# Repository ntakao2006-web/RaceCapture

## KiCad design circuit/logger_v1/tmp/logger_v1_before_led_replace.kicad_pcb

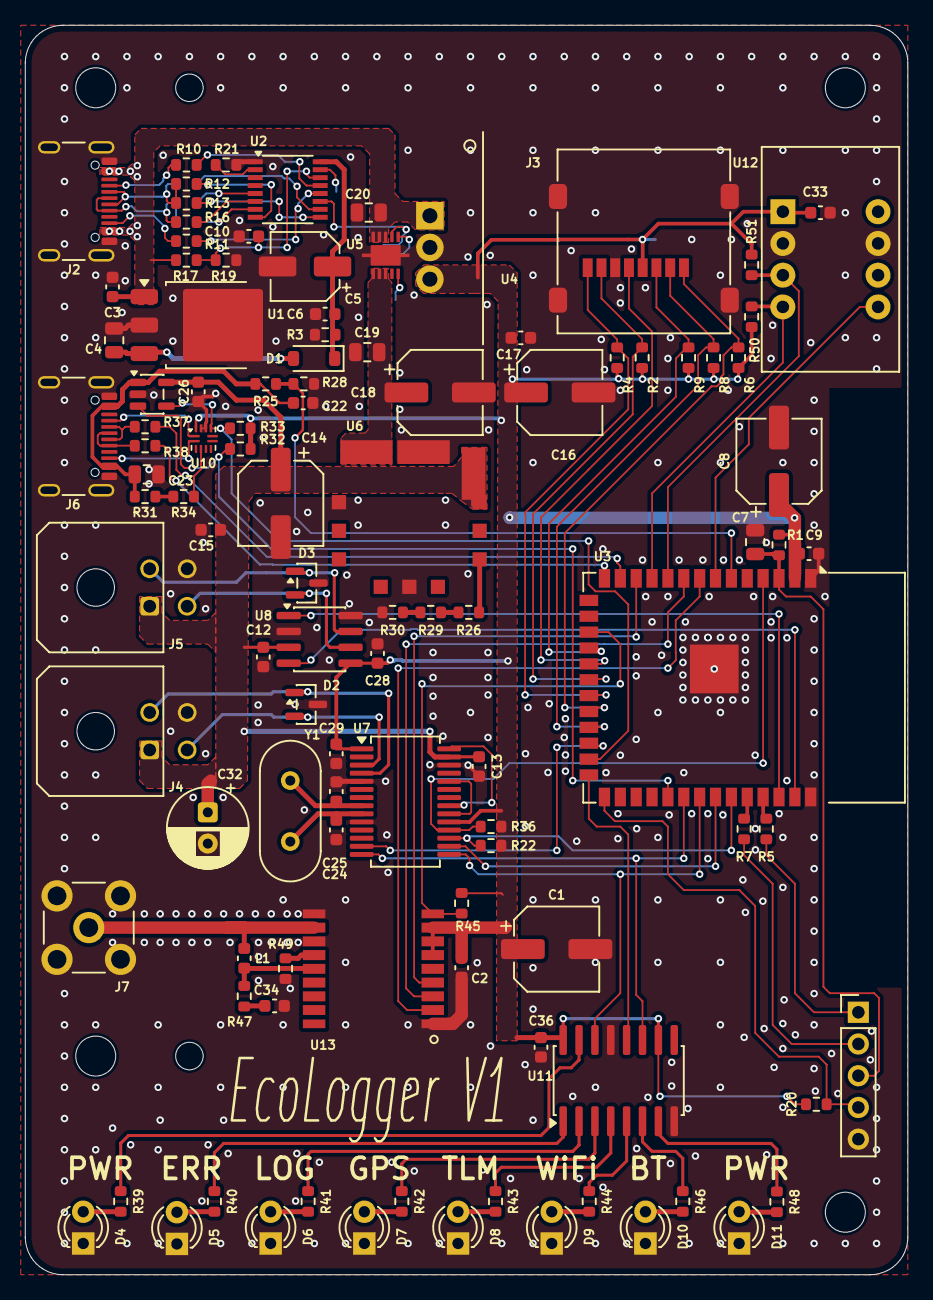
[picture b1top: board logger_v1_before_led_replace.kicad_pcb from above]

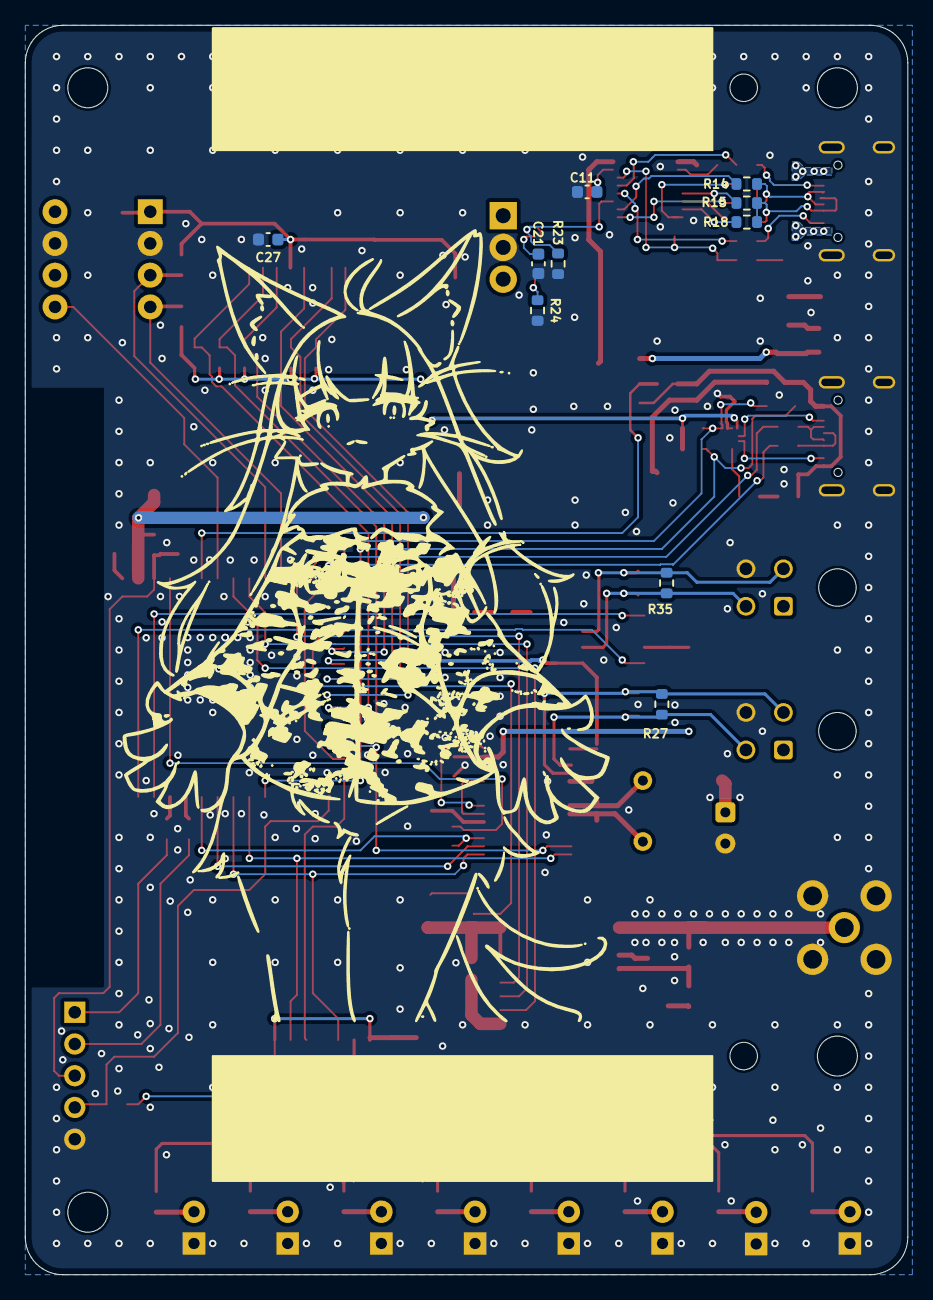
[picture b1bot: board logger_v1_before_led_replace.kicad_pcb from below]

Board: 2 copper layers, 70.6 x 100.0 mm, 123 parts (10 on the bottom side), 96 nets.

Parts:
C1, C8, C14, C16, C18: 47u; CP_Elec_6.3x5.8
C2, C3, C6, C9, C10, C12, C13, C15, C17, C22, C26, C27, C28, C29, C33, C36: 0.1u; C_0603_1608Metric
C4: 4.7u; C_0805_2012Metric
C5: 22u; CP_Elec_5x5.4
C7, C19, C20, C23: 1u; C_0805_2012Metric
C11, C21: 1n; C_0603_1608Metric
C24, C25: 33p; C_0603_1608Metric
C32: 100u; CP_Radial_D6.3mm_P2.50mm
C34: 10nF; C_0603_1608Metric
D1: PMEG4010CEGWJ; D_SOD-123
D2, D3: PEC3824C2A-AU; SOT-23
D4, D5, D6, D7, D8, D9, D10, D11: LED_Small_Filled; LED_D3.0mm
H1, H2: MountingHole; MountingHole_2.2mm_M2
H3, H4, H5, H6: MountingHole; MountingHole_3.2mm_M3
J1: Conn_01x05_Pin; PinHeader_1x05_P2.54mm_Vertical
J2, J6: 5077CR-16-SMC2-BK-TR; USB_C_5077CR-16-SMC2-BK-TR
J3: 47219-2001; Molex_47219-2001
J4, J5: 43045-0400; Molex_Micro-Fit_3.0_43045-0400_2x02_P3.00mm_Horizontal
J7: S-037-TGG; SMA_S-037-TGG_Horizontal
L1: LQW18AN27NJ00D; L_0603_1608Metric
R1, R2, R3, R4, R6, R8, R9, R20, R21, R22, R23, R32, R36, R45, R49: 10k; R_0603_1608Metric
R5, R7, R14, R15, R26, R39, R40, R41, R42, R43, R44, R46, R48, R50, R51: 1k; R_0603_1608Metric
R10, R11: 100; R_0603_1608Metric
R12, R16: 2k; R_0603_1608Metric
R13, R18: 13k; R_0603_1608Metric
R17: 49.9k; R_0603_1608Metric
R19: 4.99k; R_0603_1608Metric
R24, R25: 68k; R_0603_1608Metric
R27, R35: 120; R_0603_1608Metric
R28: 100k; R_0603_1608Metric
R29: 330; R_0603_1608Metric
R30, R47: 10; R_0603_1608Metric
R31: 390k; R_0603_1608Metric
R33: 200k; R_0603_1608Metric
R34: 510k; R_0603_1608Metric
R37, R38: 22; R_0603_1608Metric
U1: NJM2845DL1-05; TO-252-3_TabPin2
U2: LDR6321; SSOP-16_3.9x4.9mm_P0.635mm
U3: ESP32-S3-WROOM-1-N16R8; ESP32-S3-WROOM-1
U4: BP5293-33; BP5293_33_SIP3
U5: TCKE800NL; TCKE800NL_WSON10B
U6: OKL-T/6-W12N-C; OKL_T_6_W12N_C
U7: MCP25625T-E/SS; SSOP-28_5.3x10.2mm_P0.65mm
U8: ATA6561-GAQW-N; SOIC-8_3.9x4.9mm_P1.27mm
U9: TPS2041BDBVR; SOT-23-5
U10: TUSB320IRWBR; Texas_X2QFN-12_1.6x1.6mm_P0.4mm
U11: TC74HC595AF; SOIC-16W_5.3x10.2mm_P1.27mm
U12: BNO055_module; AE_BNO055_BO
U13: MAX-M10M-00B; MAX_M10M_00B_LCC18
Y1: HUSG-20.000-20; Crystal_HC49-4H_Vertical

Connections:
+3V3: C1.1, C2.1, C8.1, C9.1, C16.1, C17.1, C27.1, C28.1, C29.1, C33.1, C36.1, J3.4 (VDD), R1.1, R2.2, R4.2, R6.2, R8.2, R9.2, R20.1, R22.1, R32.1, R33.1, R36.1, R45.1, R50.2, R51.2, U3.2 (3V3), U4.3 (VOUT), U7.1 (V_{IO}), U7.19 (V_{DD}), U8.5 (VIO), U10.12 (VDD), U11.10 (~SRCLR), U11.16 (VCC), U12.1 (V_{IN}), U13.6 (V_BCKP), U13.7 (V_IO), U13.8 (VCC)
+5V: C12.1, C13.1, C14.1, C15.1, C26.1, C32.1, J4.1, J5.1, U6.4 (VOUT), U6.5 (SENSE), U7.27 (V_{DDA}), U8.3 (VCC), U9.5 (IN)
/A105_BOOT/G0: J1.4, R20.2, U3.27 (IO0)
/A105_EN: C7.1, J1.3, R1.2, U3.3 (EN)
/A105_RxD: J1.1, R5.2
/A105_TxD: J1.2, R7.2
/CAN1_RxD: U3.39 (IO1), U8.4 (RXD)
/CAN1_TxD: U3.38 (IO2), U8.1 (TXD)
/CAN2_CS: R22.2, U3.35 (IO42), U7.17 (~CS)
/CAN2_INT: U3.24 (IO47), U7.13 (~INT)
/CAN2_MISO: U3.34 (IO41), U7.16 (SO)
/CAN2_MOSI: U3.33 (IO40), U7.15 (SI), U11.14 (SER)
/CAN2_RESET: R36.2, U3.4 (IO4), U7.18 (~RESET)
/CAN2_SCK: U3.32 (IO39), U7.14 (SCK), U11.11 (SRCLK)
/CC1: R10.1, U2.13 (CC1)
/CC2: R11.1, U2.12 (CC2)
/DCDC_IN: C18.1, C19.1, U5.6 (VOUT), U5.7 (VOUT), U5.8 (VOUT), U6.2 (VIN)
/ESP_D+: R38.1, U3.14 (USB_D+)
/ESP_D-: R37.1, U3.13 (USB_D-)
/GNSS_PPS: U3.12 (IO8), U13.4 (TIMEPULSE)
/GNSS_RESET: R45.2, U3.17 (IO9), U13.9 (RESET_N)
/GNSS_RxD: U3.8 (IO15), U13.2 (TXD)
/GNSS_TxD: U3.9 (IO16), U13.3 (RXD)
/IMU_RESET: U3.7 (IO7), U12.5 (~RESET)
/IMU_SCL: R50.1, U3.11 (IO18), U12.4 (SCL/R)
/IMU_SDA: R51.1, U3.10 (IO17), U12.3 (SDA/T)
/OTG-CC1: J6.A5 (CC1), U10.1 (CC1)
/OTG-CC2: J6.B5 (CC2), U10.2 (CC2)
/OTG_OC: R32.2, U3.31 (IO38), U9.3 (~OC)
/OTG_VBUS: C22.1, C23.1, J6.A4 (VBUS), J6.A9 (VBUS), J6.B4 (VBUS), J6.B9 (VBUS), R25.1, R31.1, U9.1 (OUT)
/OTG_VBUS_SENSE: R25.2, R28.1, U3.6 (IO6)
/SD_CLK: J3.5 (CLK), U3.19 (IO11)
/SD_CMD: J3.3 (CMD), R9.1, U3.18 (IO10)
/SD_DAT0: J3.7 (DAT0), R2.1, U3.20 (IO12)
/SD_DAT1: J3.8 (DAT1), R4.1, U3.21 (IO13)
/SD_DAT2: J3.1 (DAT2), R6.1, U3.22 (IO14)
/SD_DAT3: J3.2 (DAT3/CD), R8.1, U3.23 (IO21)
/STATUS_OUT: U3.26 (IO45), U11.12 (RCLK)
/USB_ROLE: R33.2, U3.25 (IO48), U9.4 (~EN), U10.9 (ID)
/VBUS: C3.1, C20.1, J2.A4 (VBUS), J2.A9 (VBUS), J2.B4 (VBUS), J2.B9 (VBUS), R17.1, U1.1 (IN), U4.1 (VIN), U5.3 (VIN), U5.4 (VIN), U5.5 (VIN)
/VBUSEN: R23.1, U2.11 (VBUSEN), U5.2 (EN/UVLO)
GND: C1.2, C2.2, C3.2, C4.2, C5.2, C6.2, C7.2, C8.2, C9.2, C10.2, C11.2, C12.2, C13.2, C14.2, C15.2, C16.2, C17.2, C18.2, C19.2, C20.2, C21.2, C22.2, C23.2, C24.2, C25.2, C26.2, C27.2, C28.2, C29.2, C32.2, C33.2, C34.2, C36.2, D2.3 (GND), D3.3 (GND), D4.1 (K), D5.1 (K), D6.1 (K), D7.1 (K), D8.1 (K), D9.1 (K), D10.1 (K), D11.1 (K), J1.5, J2.A1 (GND), J2.A12 (GND), J2.B1 (GND), J2.B12 (GND), J2.S1 (SHIELD), J3.6 (VSS), J3.9 (SHIELD), J4.4, J5.4, J6.A1 (GND), J6.A12 (GND), J6.B1 (GND), J6.B12 (GND), J6.S1 (SHIELD), J7.2 (Ext), R3.2, R19.2, R21.2, R23.2, R24.2, R28.2, R30.2, R49.2, U1.2 (GND), U2.1 (VSS), U3.1 (GND), U3.40 (GND), U3.41 (GND), U4.2 (GND), U5.11 (GND), U6.1 (ON/OFF), U6.3 (GND), U6.7 (GND), U7.5 (STBY), U7.10 (GND), U7.26 (V_{SS}), U8.2 (GND), U8.8 (STBY), U9.2 (GND), U10.10 (GND), U10.11 (~EN), U11.8 (GND), U11.13 (~OE), U12.2 (GND), U12.7 (GND), U13.1 (GND), U13.10 (GND), U13.12 (GND)
unnamed: C34.1, R47.2
unnamed: C4.1, D1.2 (A), U1.3 (OUT)
unnamed: C5.1, C6.1, D1.1 (K), R3.1, U2.16 (VDD)
unnamed: D2.1 (LINE1), J4.2, R27.2, U7.4 (CANH)
unnamed: D2.2 (LINE2), J4.3, R27.1, U7.3 (CANL)
unnamed: D3.1 (LINE1), J5.2, R35.2, U8.7 (CANH)
unnamed: D3.2 (LINE2), J5.3, R35.1, U8.6 (CANL)
unnamed: D4.2 (A), R39.2
unnamed: D5.2 (A), R40.2
unnamed: D6.2 (A), R41.2
unnamed: D7.2 (A), R42.2
unnamed: D8.2 (A), R43.2
unnamed: D9.2 (A), R44.2
unnamed: D10.2 (A), R46.2
unnamed: D11.2 (A), R48.2
unnamed: J2.A5 (CC1), R10.2
unnamed: J2.B5 (CC2), R11.2
unnamed: J2.A6 (D+), J2.B6 (D+), R15.1, R16.1, R18.1
unnamed: J2.A7 (D-), J2.B7 (D-), R12.1, R13.1, R14.1
unnamed: J6.A6 (D+), J6.B6 (D+), R38.2
unnamed: J6.A7 (D-), J6.B7 (D-), R37.2
unnamed: J7.1 (In), L1.1, U13.11 (RF_IN)
unnamed: R26.2, R29.1
unnamed: R29.2, R30.1
unnamed: R31.2, R34.1
unnamed: R13.2, U2.9 (ADC_D-)
unnamed: R18.2, U2.7 (DOWN_D+)
unnamed: R15.2, U2.5 (EN_D+)
unnamed: C11.1, U2.15 (PDLDO)
unnamed: R16.2, U2.6 (QC_EN+)
unnamed: R12.2, U2.8 (QC_EN-)
unnamed: R14.2, U2.10 (UP_D-)
unnamed: R21.1, U2.2 (VCON0)
unnamed: C10.1, R17.2, R19.1, U2.14 (VREF)
unnamed: R7.1, U3.36 (RXD0)
unnamed: R5.1, U3.37 (TXD0)
unnamed: R24.1, U5.10 (ILIM)
unnamed: C21.1, U5.1 (dV/dT)
unnamed: R26.1, U6.6 (TRIM)
unnamed: C24.1, U7.9 (OSC1), Y1.2
unnamed: C25.1, U7.8 (OSC2), Y1.1
unnamed: U7.21 (RxCAN), U7.28 (R_{XD})
unnamed: U7.20 (TxCAN), U7.24 (T_{XD})
unnamed: R34.2, U10.4 (VBUS_DET)
unnamed: R39.1, U11.15 (QA)
unnamed: R40.1, U11.1 (QB)
unnamed: R41.1, U11.2 (QC)
unnamed: R42.1, U11.3 (QD)
unnamed: R43.1, U11.4 (QE)
unnamed: R44.1, U11.5 (QF)
unnamed: R46.1, U11.6 (QG)
unnamed: R48.1, U11.7 (QH)
unnamed: R49.1, U13.13 (LNA_EN)
unnamed: L1.2, R47.1, U13.14 (VCC_RF)

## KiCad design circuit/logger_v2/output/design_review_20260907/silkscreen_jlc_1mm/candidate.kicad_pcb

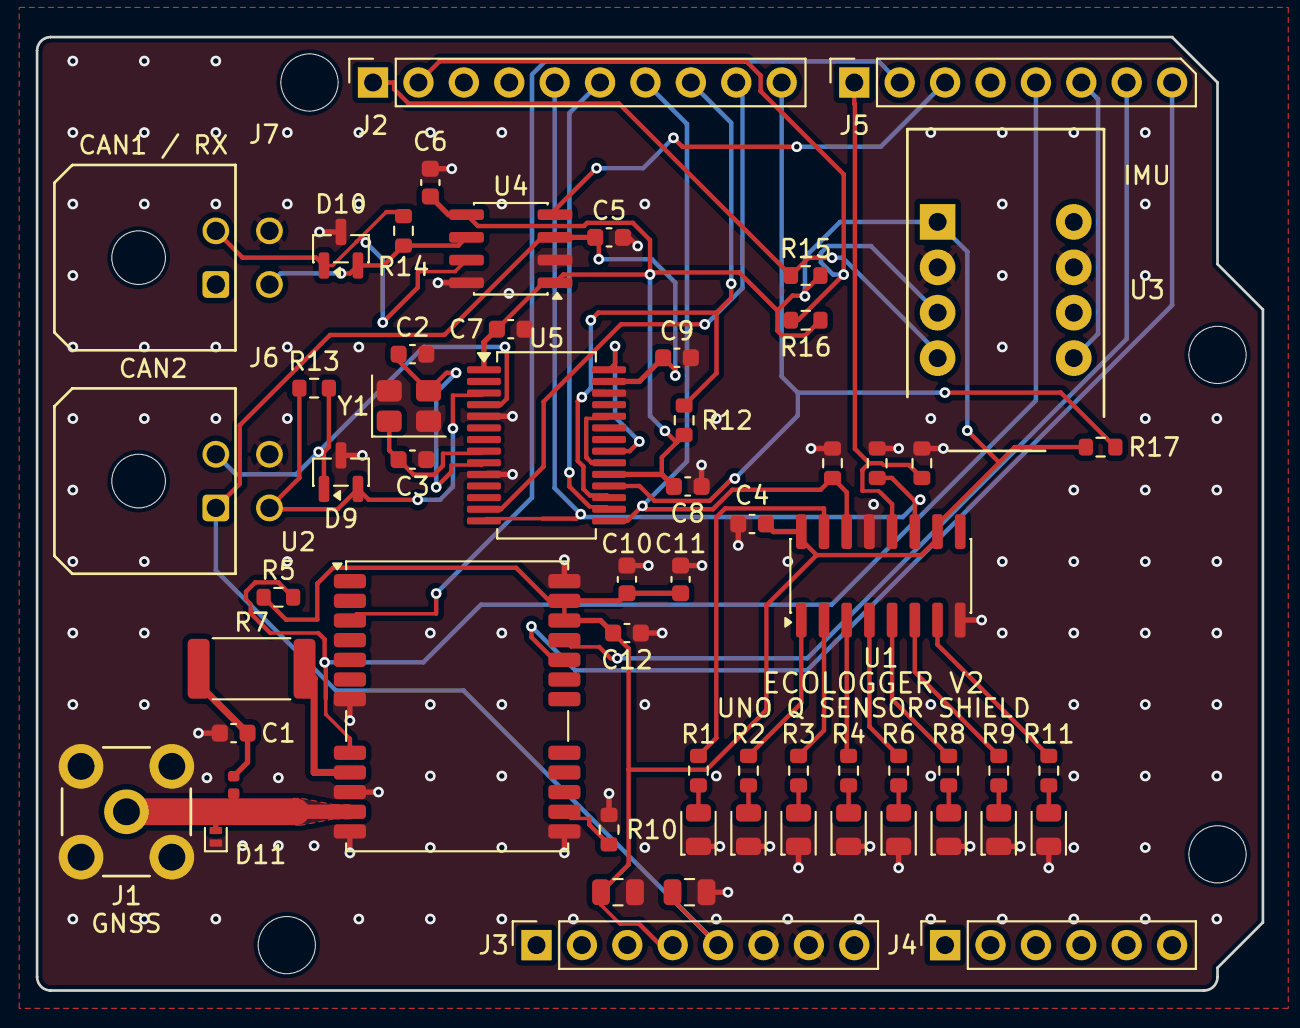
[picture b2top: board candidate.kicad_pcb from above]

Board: 2 copper layers, 68.6 x 53.3 mm, 63 parts (0 on the bottom side), 46 nets.

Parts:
C1, C4, C5, C6, C7, C8, C9, C10, C12: 100nF; C_0603_1608Metric
C2, C3: 18pF; C_0603_1608Metric
C11: 1uF; C_0603_1608Metric
C13, C14: 10uF; C_0805_2012Metric
D1, D2, D3, D4, D5, D6, D7, D8: GREEN 0805; LED_0805_2012Metric_ShieldSilk
D9, D10: NUP2105LT1G; SOT-23
D11: RF ESD; D_SOD-882
J1: S-037-TGG; SMA_S-037-TGG_Horizontal
J2: Digital/PWM; PinSocket_1x10_P2.54mm_Vertical
J3: Power; PinSocket_1x08_P2.54mm_Vertical
J4: Analog; PinSocket_1x06_P2.54mm_Vertical
J5: Digital/PWM; PinSocket_1x08_P2.54mm_Vertical_ShieldSilk
J6, J7: 43045-0400; Molex_Micro-Fit_3.0_43045-0400_2x02_P3.00mm_Horizontal
L1: 27nH; L_0402_1005Metric
MH1, MH2, MH3, MH4: MountingHole_3.2mm
R1, R2, R3, R4, R6, R8, R9, R11: 680R; R_0603_1608Metric
R5, R10, R12, R17: 10k; R_0603_1608Metric
R7: 27R 1W; R_2512_6332Metric
R13, R14: 120; R_0603_1608Metric
R15, R16: 4.7k; R_0603_1608Metric
R18, R19, R20: 47k; R_0603_1608Metric
U1: 74HC595D,118; SOIC-16_3.9x9.9mm_P1.27mm
U2: NEO-M9N-00B; ublox_NEO
U3: BNO055_module; AE_BNO055_BO_ShieldSilk
U4: ATA6561-GAQW; SOIC-8_3.9x4.9mm_P1.27mm
U5: MCP25625-E/SS; SSOP-28_5.3x10.2mm_P0.65mm
Y1: 20MHz 12pF; Crystal_SMD_3225-4Pin_3.2x2.5mm

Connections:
+3V3: C4.1, C6.1, C7.1, C8.1, C10.1, C11.1, C12.1, C13.1, J3.4, R5.1, R12.1, R15.2, R16.2, R17.1, U1.10, U1.16, U2.22, U2.23, U3.1, U4.1, U4.5, U5.1, U5.19
+5V: C5.1, C9.1, C14.1, J3.5, J6.1, U4.3, U5.27
/CAN1_RXD: J5.3, U4.4
/CAN2_CS_N: J2.8, R12.2, U5.17
/CAN2_INT_N: J2.9, U5.13
/CAN2_RESET_N: J2.10, R17.2, U5.18
/GNSS_PPS: J5.2, U2.3
/GNSS_RESET_N: J5.5, R5.2, U2.8
/GNSS_RF: D11.2, J1.1, L1.1, U2.11
/GNSS_RXD: J5.7, U2.21
/GNSS_TXD: J5.8, U2.20
/IMU_RESET_N: J5.6, U3.5
/IMU_SCL: J2.1, R15.1, U3.4
/IMU_SDA: J2.2, R16.1, U3.3
/SPI2_MISO: J2.6, U5.16
/SPI2_MOSI: J2.7, R18.1, U1.14, U5.15
/SPI2_SCK: J2.5, R19.1, U1.11, U5.14
/STATUS_LATCH: J5.1, R20.1, U1.12
GND: C1.2, C2.2, C3.2, C4.2, C5.2, C6.2, C7.2, C8.2, C9.2, C10.2, C11.2, C12.2, C13.2, C14.2, D1.1, D2.1, D3.1, D4.1, D5.1, D6.1, D7.1, D8.1, D9.3, D10.3, D11.1, J1.2, J2.4, J3.6, J3.7, J6.4, J7.4, R10.2, R18.2, R19.2, R20.2, U1.8, U1.13, U2.7, U2.10, U2.12, U2.13, U2.24, U3.2, U3.7, U4.2, U4.8, U5.5, U5.10, U5.26, Y1.2, Y1.4
unnamed: C1.1, L1.2, R7.2
unnamed: D1.2, R1.2
unnamed: D2.2, R2.2
unnamed: D3.2, R3.2
unnamed: D4.2, R4.2
unnamed: D5.2, R6.2
unnamed: D6.2, R8.2
unnamed: D7.2, R9.2
unnamed: D8.2, R11.2
unnamed: D9.1, J6.2, R13.2, U5.4
unnamed: D9.2, J6.3, R13.1, U5.3
unnamed: D10.1, J7.2, R14.2, U4.7
unnamed: D10.2, J7.3, R14.1, U4.6
unnamed: R1.1, U1.15
unnamed: R2.1, U1.1
unnamed: R3.1, U1.2
unnamed: R4.1, U1.3
unnamed: R6.1, U1.4
unnamed: R8.1, U1.5
unnamed: R9.1, U1.6
unnamed: R11.1, U1.7
unnamed: R10.1, U2.14
unnamed: R7.1, U2.9
unnamed: C2.1, U5.9, Y1.3
unnamed: C3.1, U5.8, Y1.1
unnamed: U5.21, U5.28
unnamed: U5.20, U5.24

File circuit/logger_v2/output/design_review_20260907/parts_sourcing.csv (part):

"Reference","Existing_part","Proposed_part","Manufacturer","LCSC","JLC_library","JLC_assembly","Package","Stock_reported","Stock_evidence","Checked_JST","Status","URL","Notes"
"U1","TC74HC595AF","74HC595D,118","Nexperia","C5947","Basic","Economic and Standard","SOIC-16 3.9mm","302263","JLC indexed page snapshot","2026-09-07","Selected final design","https://jlcpcb.com/partdetail/Nexperia-74HC595D118/C5947","Change footprint from 5.3mm SOP; same logic pinout"
"U2","NEO-M9N-00B","NEO-M9N-00B","u-blox","C5119087","Extended","Standard Only","SMD-24P","500","JLC indexed page snapshot; current page confirms Standard Only","2026-09-07","Selected final design","https://jlcpcb.com/partdetail/UBLOX-NEO_M9N00B/C5119087","LCSC separately showed 322; do not confuse supplier stock with allocated PCBA stock"
"U3","AE-BNO055-BO","AE-BNO055-BO","Akizuki","","Unconfirmed","Excluded from SMT BOM/CPL; post-assembly","18x11mm module","TBD","No exact JLC registration verified","2026-09-07","Selected post-assembly","https://akizukidenshi.com/catalog/g/g116996/","Use module-specific BOM; never assign bare BNO055 C93216 to this footprint"
"U3 alternative","AE-BNO055-BO","BNO055","Bosch Sensortec","C93216","Extended","Standard Only","LGA-28 5.2x3.8mm","8957","JLC category indexed stock snapshot","2026-09-07","Alternative only","https://jlcpcb.com/partdetail/BoschSensortec-BNO055/C93216","Requires full circuit redesign around same sensor IC and axis validation"
"U4","ATA6561-GAQW-N","ATA6561-GAQW","Microchip","C2929602","Extended","SMT listed; service class not displayed","SOIC-8","1117","LCSC stock only; JLC quantity not displayed","2026-09-07","Selected final design","https://jlcpcb.com/partdetail/MicrochipTech-ATA6561GAQW/C2929602","AEC-Q100 version instead of industrial -N; confirm ordering allocation"
"U5","MCP25625T-E/SS","MCP25625-E/SS","Microchip","C184944","Extended","Economic and Standard","SSOP-28 5.3mm","86","JLC indexed page snapshot; indexed 10 months ago","2026-09-07","Selected final design","https://jlcpcb.com/partdetail/MicrochipTech-MCP25625_ESS/C184944","T suffix changes reel packaging; same IC and SSOP; stock must be refreshed at order"
"D1-D8","3mm THT LED","KT-0805G","Hubei KENTO","C2297","Basic","Economic and Standard","0805","1845064","JLC category page indexed today","2026-09-07","Selected final design","https://jlcpcb.com/partdetail/KT-0805G/C2297","Green Vf2.6-3.1V at5mA; selected680ohm resistors; verify actual low-current brightness"
"D9-D10","PEC3824C2A-AU","NUP2105LT1G","onsemi","C14486","Extended","SMT listed","SOT-23","190745","JLC indexed page snapshot","2026-09-07","Selected final design","https://jlcpcb.com/partdetail/NUP2105LT1G/C14486","Pin1/2 line pin3 common; 24V 30pF max; standard part is not SZ automotive-qualified variant"
"D11","new RF ESD","PESD5V0F1BL,315","Nexperia","C45961","Extended","Economic and Standard","SOD882 DFN1006-2","18223","JLC indexed page snapshot","2026-09-07","Selected final design","https://jlcpcb.com/partdetail/Nexperia-PESD5V0F1BL315/C45961","0.4pF typ bidirectional RF ESD; mount at SMA"
"L1","27nH unspecified","LQG15HS27NJ02D","Murata","C12669","Extended","Economic and Standard","0402","InStock quantity unverified","Current JLC structured availability; no quantity displayed","2026-09-07","Selected final design","https://jlcpcb.com/partdetail/LQG15HS27NJ02D/C12669","27nH 350mA DCR0.46ohm SRF1.7GHz; footprint changes from0603"
"L1 alternate","27nH unspecified","LQG15HZ27NH02D","Murata","C237452","Extended","Economic and Standard","0402","1096","JLC indexed page snapshot","2026-09-07","Alternative if allocation unavailable","https://jlcpcb.com/partdetail/MurataElectronics-LQG15HZ27NH0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","27nH 3percent AEC-Q200; confirm RF curve for final selected choke"
"Y1","HUSG-20.000-20","XC2EL89COO-114YLC-20M","YXC","C18213008","Extended","Economic and Standard","SMD3225-4P","4098","JLC indexed page snapshot","2026-09-07","Selected final design","https://jlcpcb.com/partdetail/19387115-XC2EL89COO_114YLC20M/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","20MHz CL12pF ESR70ohm -40to125C; C2/C3 must match12pF load"
"Y1 alternate","HUSG-20.000-20","ABM8G-20.000MHZ-18-D2Y-T","Abracon","C1985763","Extended","Economic and Standard","SMD3225-4P","13","JLC indexed page snapshot; available order qty10","2026-09-07","CL18pF alternative limited stock","https://jlcpcb.com/partdetail/AbraconLLC-ABM8G_20_000MHZ_18_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","20MHz CL18pF ESR80ohm -40to85C"
"J1","S-037-TGG","S-037-TGG","COSMTEC","","Unconfirmed","Excluded from SMT BOM/CPL; post-assembly","Horizontal THT SMA","TBD","No exact JLC registration verified","2026-09-07","Selected post-assembly; orientation fixed","https://akizukidenshi.com/goodsaffix/S-037-TGG_20220729.pdf","Do not substitute generic SMA without comparing manufacturer dimensions and RF launch"
"J2-J5","UNO shield headers","UNO shield stacking headers","TBD","","Unconfirmed","Excluded from SMT BOM/CPL; post-assembly","2.54mm long-tail stacking headers","TBD","Exact manufacturer and part not specified","2026-09-07","Selected post-assembly; orientation fixed","https://docs.arduino.cc/hardware/uno-q/","Sockets alone may not provide required male shield tails; verify stand-off and UNO Q clearance"
"J6-J7","43045-0400","43045-0400","Molex","","Unconfirmed","Excluded from SMT BOM/CPL; post-assembly","Micro-Fit3.0 2x2 horizontal","TBD","No exact JLC registration verified","2026-09-07","Selected post-assembly; orientation fixed","https://www.molex.com/en-us/products/part-detail/430450400","Check exact suffix and board retention features before matching procurement alternates"
"R7 rejected original value","22R 1W","25121WJ0220T4E","UNI-ROYAL","C27258","Extended","Unconfirmed","2512","InStock quantity hidden","Current JLC HTML structured availability; separate LCSC indexed stock86200","2026-09-07","Not selected; insufficient tolerance margin","https://jlcpcb.com/partdetail/28007-25121WJ0220T4E/C27258","22ohm5%1W; 22R nominal does not prove below150mA including tolerances"
"R7","22R 1W","25121WJ0270T4E","UNI-ROYAL","C25478","Extended","Unconfirmed","2512","InStock quantity hidden","Current JLC HTML structured availability","2026-09-07","Selected final design","https://jlcpcb.com/partdetail/C25478","27ohm5%1W; below141mA at3.6V ignoring other resistance but antenna voltage lower by0.10V at20mA"
"C1/C4/C5/C6/C7/C8/C9/C10/C12","100nF or new","CC0603KRX7R9BB104","YAGEO","C14663","Basic","Economic and Standard","0603","65537578","JLC indexed today; available order51319038","2026-09-07","Selected final design","https://jlcpcb.com/partdetail/Yageo-CC0603KRX7R9BB104/C14663","100nF X7R50V10%; C1 RF bias capacitor may share this part"
"C11","new1uF","CL10A105KB8NNNC","Samsung Electro-Mechanics","C15849","Basic","Economic and Standard","0603","9147549","JLC indexed today; available order6454019","2026-09-07","Selected final design","https://jlcpcb.com/partdetail/C15849","1uF X5R50V10%; maximum rated temperature85C"
"C13/C14","new10uF","CL21A106KAYNNNE","Samsung Electro-Mechanics","C15850","Basic","Economic and Standard","0805","7852178","JLC indexed today; available order6491601","2026-09-07","Selected final design","https://jlcpcb.com/partdetail/CL21A106KAYNNNE/C15850","10uF X5R25V10%; account for DC bias; maximum rated temperature85C"
"R18/R19/R20","new47k","0603WAF4702T5E","UNI-ROYAL","C25819","Basic","Economic and Standard","0603","InStock quantity hidden","Current JLC HTML structured availability","2026-09-07","Selected final design","https://jlcpcb.com/partdetail/C25819","47k1%100mW"
"R1/R2/R3/R4/R6/R8/R9/R11","1k","0603WAF6800T5E","UNI-ROYAL","C23228","Basic","Economic and Standard","0603","InStock quantity hidden","Current JLC HTML structured availability","2026-09-07","Selected final design","https://jlcpcb.com/partdetail/0603WAF6800T5E/C23228","680ohm1%100mW; verify actual LED brightness"
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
